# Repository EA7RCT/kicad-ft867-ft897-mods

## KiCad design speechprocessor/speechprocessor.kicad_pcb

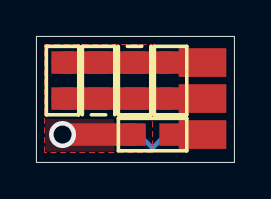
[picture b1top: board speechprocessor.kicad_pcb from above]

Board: 2 copper layers, 11.0 x 7.0 mm, 6 parts (1 on the bottom side), 3 nets.

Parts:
C1, C2: 150p; SMD_0805
D1, D2: BAT85; SMD_0805_Polarized
Ref**: andresgongora
e: 680k; SMD_0805

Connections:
Earth: C2.2, Ref**.0
unnamed: C1.1, D1.2, D2.1, e.2
unnamed: C1.2, D1.1, D2.2, e.1

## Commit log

2020-11-28 Add submodule
2020-11-28 Update library
2020-11-28 First iteration of speechprocessor
2020-12-28 Update for manufacture
